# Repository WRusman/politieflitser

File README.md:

# politieflitser
Printontwerp voor een driedubbele astabiele multivibrator die knippert zoals zwaailichten van de politie

Wat heb je nodig :

- de printplaat
- 6x weerstand 33 Kilo Ohm (oranje - oranje - oranje) 
- 6x weerstand 4,7 Kilo Ohm (geel - violet - rood)
- 2x weerstand 470 Ohm (geel - violet - bruin)
- 4x weerstand 1 Kilo Ohm (bruin - zwart - rood)
- 2 Electolytische Condensatoren van 100 MicroFarad (µF)
- 4 Electolytische Condensatoren van 10 MicroFarad (µF)
- 2x transistor BC327 (ook te herkennen aan gouden bovenkant)
- 2x transistor BC337 (ook te herkennen aan zilveren bovenkant)
- 6x transistor BC547
- 2 grote blauwe leds

Op de printplaat zie je diverse teksten staan bij de onderdelen:

R1 t/m R18; dit zijn de weerstanden. Het maakt niet uit hoe je deze monteert, ze hebben geen + of – polen. Al ziet het er natuurlijk wel mooi uit als alle kleuren aan dezelfde kant zitten.

C1 t/m C6; dit zijn de electrolytische condensatoren (elco). Monteer deze zo dat het witte vlak op de printplaat overeen komt met de minpool van de condensator; dat is de witte streep op de elco. 

Q1 t/m Q10; dit zijn de transistoren. Monteer deze zo dat de platte kant van de transistor overeenkomt met de platte kant van de contour op de printplaat. Het middelste pootje komt in het gaatje tegenover de platte kant, de twee buitenste pootjes komen in de gaatjes aan de zijkant van de contour.

D1 en D2; dit zijn de Light Emitting Diodes (LED’s). Monteer deze zo dat de platte kant van de LED overeenkomt met de platte kant van de contour op de printplaat, een tweede aanwijzing is de K bij de contour van de LED, die komt overeen met de Kathode, wat toevallig ook het Kortste pootje is 

De onderdelen moeten op de kant komen waar de teksten staan, dus niet aan de kant met de koper sporen. Het opbouwen begint meestal met de laagste componenten, zodat je niet tussen hoge dingen in hoeft te werken. In dit geval zijn de weerstanden het laagst dus daar beginnen we mee. 

Buig de draden van de weerstand na het dikke deel strak in een hoek van 90 graden, buig ze niet te vaak heen en weer want dan kunnen ze afbreken! Steek de draden door de gaatje en buig de draden aan de kant van de koper sporen op de print een klein beetje naar buiten, zo vallen ze er minder makkelijk uit. Soldeer de weerstand vast, hou de soldeerbout niet te lang op de printplaat want anders kunnen de koperen sporen los laten van de printplaat.

- Begin met de 6 weerstanden R3, R4, R8, R9, R13 en R14 deze hebben een waarde
  van 33k (or-or-or)

- Daarna de 6 weerstanden R2, R5, R7, R10, R12 en R15, deze hebben een waarde
  van 4,7k (ge-vi-ro)

- Daarna de 4 weerstanden R1, R6, R11 en R16, deze hebben een waarde
  van 1k (br-zw-ro)

- Als laatste de 2 weerstanden R17 en R18, deze hebben een waarde
  van 470 Ohm (ge-vi-br)

Als tweede stap gaan we de transistoren plaatsen.

- Begin met Q3 en Q4, dat zijn de BC327 transistoren, in dit pakketje ook te herkennen aan de
  goudkleurige bovenkant.

- Daarna Q1 en Q2, dat zijn de BC337 transistoren, in dit pakketje ook te herkennen aan de
  zilverkleurige bovenkant.

- Als laatste Q5 t/m Q10, dat zijn de BC547 transitoren met een zwarte bovenkant.

Als derde stap gaan we de elco’s plaatsen.
- Begin met de 100 µF elco’s C3 en C4, deze hebben de meest lastige plek. Zorg dat de witte streep
  op de elco (minpool) aan de kant van het witte vlak zit.

- Daarna de 10 µF elco’s C1, C2, C5 en C6. Zorg ook hier dat de witte streep
  op de elco (minpool) aan de kant van het witte vlak zit.

Als laatste stap kunnen we de LED’s plaatsen, zorg dat de vlakke kant van de LED op de vlakke kant van de countour zit, of op korte poot bij de K en dus naar de buitenkant van de print gericht.

Nu nog de draden van de batterijclip met de rode draad aan de + aansluiting en met de zwarte draad aan de – aansluiting, en dan zou alles moeten werken.

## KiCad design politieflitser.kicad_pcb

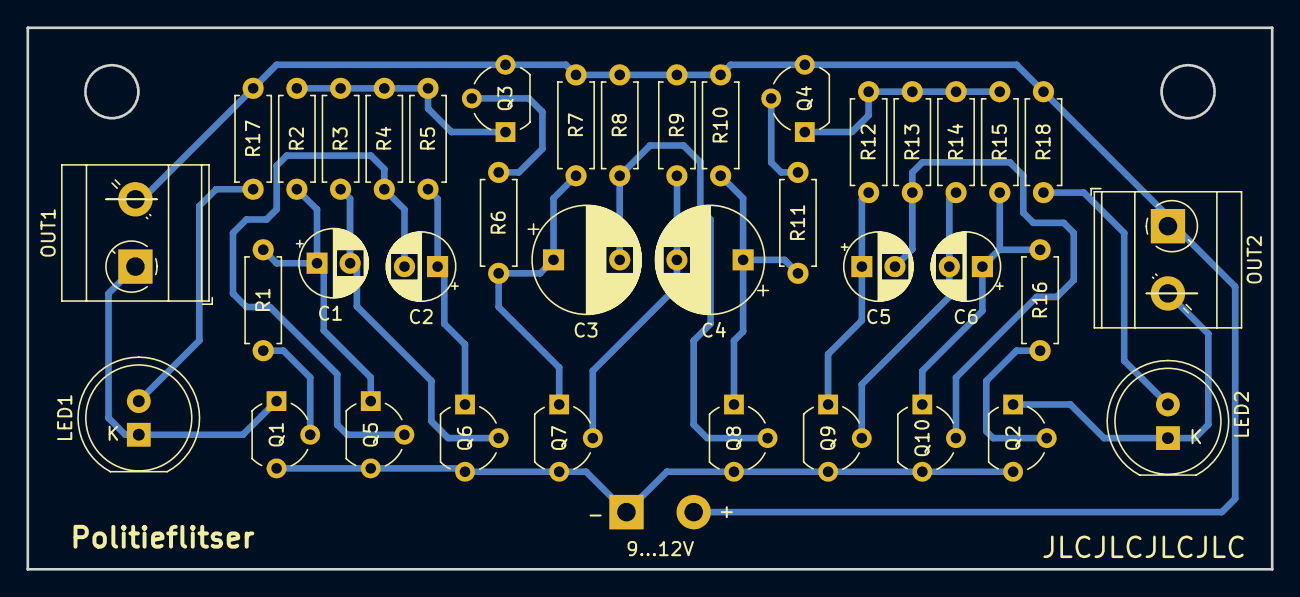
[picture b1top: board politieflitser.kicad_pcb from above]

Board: 2 copper layers, 94.0 x 40.9 mm, 39 parts (0 on the bottom side), 24 nets.

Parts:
9...12V: 12V; TerminalBlock_MetzConnect_Type073_RT02602HBLU_1x02_P5.08mm_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
C1, C2, C5, C6: 10u; CP_Radial_D5.0mm_P2.50mm
C3, C4: 100u; CP_Radial_D8.0mm_P5.00mm
LED1, LED2: LED; LED_D8.0mm
OUT1: OUTPUT1; TerminalBlock_MetzConnect_Type073_RT02602HBLU_1x02_P5.08mm_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
OUT2: OUTPUT2; TerminalBlock_MetzConnect_Type073_RT02602HBLU_1x02_P5.08mm_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
Q1, Q2: BC337; TO-92_Wide
Q3, Q4: BC327; TO-92_Wide
Q5, Q6, Q7, Q8, Q9, Q10: BC547; TO-92_Wide
R1: 1K; R_Axial_DIN0207_L6.3mm_D2.5mm_P7.62mm_Horizontal
R2: 4K7; R_Axial_DIN0207_L6.3mm_D2.5mm_P7.62mm_Horizontal
R3, R4: 33K; R_Axial_DIN0207_L6.3mm_D2.5mm_P7.62mm_Horizontal
R5, R7, R10, R12, R15: 4k7; R_Axial_DIN0207_L6.3mm_D2.5mm_P7.62mm_Horizontal
R6, R11, R16: 1k; R_Axial_DIN0207_L6.3mm_D2.5mm_P7.62mm_Horizontal
R8, R9, R13, R14: 33k; R_Axial_DIN0207_L6.3mm_D2.5mm_P7.62mm_Horizontal
R17, R18: 470; R_Axial_DIN0207_L6.3mm_D2.5mm_P7.62mm_Horizontal

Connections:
+12V: 9...12V.2, OUT1.2, OUT2.1, Q3.3 (E), Q4.3 (E), R7.1, R8.1, R9.1, R10.1, R17.1, R18.1
GND: 9...12V.1, Q1.3 (E), Q2.3 (E), Q5.3 (E), Q6.3 (E), Q7.3 (E), Q8.3 (E), Q9.3 (E), Q10.3 (E)
unnamed: LED2.2 (A), R18.2
unnamed: LED2.1 (K), OUT2.2, Q2.1 (C)
unnamed: LED1.2 (A), R17.2
unnamed: LED1.1 (K), OUT1.1, Q1.1 (C)
unnamed: Q1.2 (B), R1.1
unnamed: Q2.2 (B), R16.2
unnamed: Q3.2 (B), R6.1
unnamed: Q3.1 (C), R2.1, R3.1, R4.1, R5.1
unnamed: Q4.2 (B), R11.2
unnamed: Q4.1 (C), R12.1, R13.1, R14.1, R15.1
unnamed: C2.2, Q5.2 (B), R4.2
unnamed: C1.1, Q5.1 (C), R1.2, R2.2
unnamed: C1.2, Q6.2 (B), R3.2
unnamed: C2.1, Q6.1 (C), R5.2
unnamed: C4.2, Q7.2 (B), R9.2
unnamed: C3.1, Q7.1 (C), R6.2, R7.2
unnamed: C3.2, Q8.2 (B), R8.2
unnamed: C4.1, Q8.1 (C), R10.2, R11.1
unnamed: C6.2, Q9.2 (B), R14.2
unnamed: C5.1, Q9.1 (C), R12.2
unnamed: C5.2, Q10.2 (B), R13.2
unnamed: C6.1, Q10.1 (C), R15.2, R16.1
